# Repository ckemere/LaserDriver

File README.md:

# Glance out

The output side of **Glance**: stimulation HATs for the Raspberry Pi, their power boards, the MCU firmware and the Pi
software and OS images.  A Pi 4 with one of these HATs delivers timed optogenetic laser pulses or isolated
constant-current electrical stimulation, triggered from the Pi, a BNC input or the network, with an OLED and joystick
for use at the rig.

| | |
|---|---|
|  |  |
| **StimHAT** — isolated constant-current stimulator | **LaserDriverHAT** — laser-diode driver |
|  |  |
| **DCDCPod** — isolated ±15 V supply pod for the StimHAT | **SimpleBatteryPack** — battery ±V supply for the StimHAT |

## The boards

**StimHAT** (`hardware/StimHAT/`).  A 65 × 57 mm four-layer HAT.  The west half is the shared core: an MSPM0G1507
microcontroller on the Pi's UART with its own USB-C port and CH340N for stand-alone use, the HAT ID EEPROM, BNC
trigger in and sync out, a five-way joystick and a FIRE button, and either the Adafruit OLED bonnet stacked above or a
0.91" OLED module on the board.  The east half, behind a 2.5 mm isolation barrier crossed only by two digital
isolators, is a cathodic-first biphasic constant-current stimulator: a DAC60501 set-point, an OPA2192 current source
with a 2.49 kΩ sense resistor (502 µA full scale, 0.12 µA per code), a DG418 shorting switch between pulses and a
window comparator that latches a fault when the electrode voltage leaves ±12.35 V.  The isolated side takes its ±V
from the DCDCPod or the SimpleBatteryPack.

**LaserDriverHAT** (`hardware/LaserDriverHAT/`).  The same core with the laser-diode driver in place of the
stimulator: an MT3608 boost to 12 V, a TLV2371 current servo on a 2 Ω shunt set by the MCU's DAC (about 100 mA per
volt), a dual-FET switch pair for pulse and dummy load driven by a hardware timer, and a photodiode monitor.  The
driver block is the hand-made layout of the earlier plug-in laser module, carried over intact.

**DCDCPod** (`hardware/DCDCPod/`).  A 31 × 22.5 mm board that stands on the StimHAT between the OLED bonnet and the
BNCs: a RECOM RB-0515D/HP 5 V → ±15 V converter, an LC filter and a capacitance multiplier per rail, giving quiet
±13.5 V for the stimulator from the Pi's 5 V.

**SimpleBatteryPack** (`hardware/SimpleBatteryPack/`).  Two 4S packs in series with a centre tap, an ON/OFF switch and
a gauge, for a fully battery-powered stimulator when even the pod's residual ripple matters.

## Software

- **Firmware** (`firmware/`): one source tree builds the three MCU images (`BOARD=stim|laser|rev2`).  The MCU keeps
  the pulse timing, state machine and safety interlocks; the Pi only configures and triggers.  The binary protocol in
  `firmware/protocol.h` is mirrored by `pi/protocol.py` and cross-checked in CI.
- **Pi** (`pi/`): the `laserhat` Debian package — a C broker that owns the UART and the trigger GPIOs and accepts
  low-latency UDP triggers, an OLED daemon, a web GUI, `laserhat-flash` (programs the MCU over SWD from the Pi's
  GPIOs) and `laserhat-eeprom` (programs the HAT ID EEPROM).  The board type comes from the EEPROM; the firmware
  reports its own and the two are cross-checked.
- **Releases**: a `v*` tag makes CI build the debs and golden Raspberry Pi OS images (`laserhat-raspios-lite-*.img.xz`)
  with everything installed.  Flash an image, boot, program the EEPROM once, run `sudo laserhat-flash`.

## Getting started

1. Flash the latest release image to a card and boot the Pi with the HAT fitted.
2. Program the HAT's identity once: `sudo laserhat-eeprom write stim --yes` (or `laser`) with JP1 open, close JP1,
   reboot.  `laserhat-eeprom read` shows what the Pi sees.
3. `sudo laserhat-flash` programs the matching firmware and reports the MCU's version and board.
4. Open the web GUI (port 80 on the Pi) or use the joystick and OLED; triggers come from the FIRE button, the TRIG IN
   BNC, Pi GPIO 18, or UDP on the wired port.

`pi/PROVISIONING.md` has the details (services, network, displays, EEPROM buses), `hardware/<board>/README.md` the
design notes, pin maps and audit records of each board, `docs/REPO_MAP.md` the directory index, and `CLAUDE.md` the
working guide for agents.

## History

The first generations — a HAT with plug-in laser and e-stim modules and a relay-switched battery pack — are archived at
tag `archive/pre-glance-cleanup`, with their design history in `docs/history/REV2_NOTES.md`.  Software identifiers
(`laserhat` package, commands, services and variables) keep those names for now.

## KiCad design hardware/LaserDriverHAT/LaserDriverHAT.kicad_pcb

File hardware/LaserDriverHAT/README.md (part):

# LaserDriverHAT — the LaserHAT Rev 2 core and the LaserDaughter laser-diode driver on one Raspberry Pi HAT (rev A, 2026-10-30)

One 65 × 57 mm, 4-layer HAT derived from the StimHAT (`../StimHAT/`): the StimHAT's HAT core — MSPM0G1507, CH340N
USB-UART, USB-C power path, HAT ID EEPROM, joystick / FIRE / BSL buttons, LEDs, BNC trigger in and sync out, OLED socket,
owl — kept footprint for footprint and track for track, the isolated e-stim stimulator removed, and the laser-diode driver
of the plug-in module `../LaserDaughter/` (archived, tag `archive/pre-glance-cleanup`; rev 2.0, ordered 2026-10-01) brought in as its hand-made layout block.  The
Adafruit 4567 OLED bonnet stacks on the Pi header as on the StimHAT.  **Status: placed, the laser block's own copper
intact; the seven connections between the block and the HAT core were hand-routed by the user.  Ordered 2026-11-01 (rev 3), verified 2026-11-11 (laser output, buttons, displays).**

## Files

Generated like the StimHAT: `sch_parts.py` (single source of truth: parts, values, footprints, LCSC codes, pin → net) +
`sch_symbols.py` + `sch_engine.py` → `gen_schematic.py` writes `LaserDriverHAT.kicad_sch` and `laserdriverhat.kicad_sym`
(deterministic UUIDs: the HAT-core symbols keep the StimHAT's UUIDs).  `tools/netcheck.py` (drawing = `sch_parts`),
`tools/pcb_sync.py --keep-tracks` (headless F8, matches by reference), `tools/fresh_uuids.py`, `tools/stamp_fields.py`,
`tools/place.py` (placement table, outline, GND plane / pours, standoff keep-outs, silk, bonnet drawing; idempotent and
in sync with the board), `tools/project_settings.py` (net classes in the `.kicad_pro`; **Power1A** = the HAT core's +5V, VBUS,
VBUS_SW, +3V3, MSPM0_3V3, +3V3_PI (as on the StimHAT), +12V, /SW, LASER_V and the drive path /LD_CATHODE, /DUMMY_TOP / _MID / _BOT,
/LaserDrive, /IDrive, sized for 1 A: 0.5 mm, vias 0.8 / 0.4; `LaserDriverHAT.kicad_dru` enforces >= 0.5 mm outer / >= 1.0 mm
inner, 0.25 mm allowed on an outer layer inside an IC's courtyard for the neck-down to fine-pitch pins - the same rules as the StimHAT), `tools/make_footprints.py`
(`laserdriverhat.pretty`: MSPM0 VQFN-32, ALPS joystick, right-angle BNC; the owl G1 is `Footprints:OwlLogo_Eyes_14mm_R` from `../tools/owl_logo.py`),
`tools/make_bom.py` → `bom_LaserDriverHAT.csv`, `tools/make_fab.py` → `../fab/LaserDriverHAT/` (gerbers zip, JLC BOM / CPL,
3D renders `LaserDriverHAT_top.png` / `_bottom.png`), `tools/drc_summary.py`, `tools/fixups.py` / `maze_nets.py` / `stitch.py`
(hand-routing helpers).  The library nickname is `laserdriverhat` (was `stimhat`).  `LaserDriverHAT.kicad_dru`: one thermal
spoke allowed on the outer pours, and on R202 (see "Checks").  The StimHAT's Freerouting tools (autoroute, fan-out,
pre-route) and `board_init.py` were not carried over: they built the e-stim side.

## What changed against the StimHAT

**Removed** (schematic, board, BOM): the whole isolated half — U101 ISO7741F, U104 TLV76050, U105 DAC60501, U106 OPA2192,
U107 CD74HC4053, U108 DG418, U109 ISO1640, U110 TLV1702, R101–R121, C101–C127, D101–D104, J101 (electrodes), J102 (battery
/ DC-DC pod), J103 (pod 5 V), TP101 / TP102; the nets of the isolated side (GND_ISO, ±V_STIM, ±5V_ISO, …) and the six
HAT-side isolator lines (EN_H, CATH_H, RELEASE_H, FAULT_H, SDA_H, SCL_H); the isolation barrier (keep-out strips,
`hat_region` / `isolated_region` rule areas, the `.kicad_dru` barrier and `tht_connectors` / `j102_one_spoke` rules), the
Isolated / IsolatedPower / Rails net classes, the ISOLATED / NYLON / J102 / J103 silk, the DC-DC pod drawing.  On the board
360 StimHAT tracks / vias went with them (every one of a vanished net, BUTTON3's old route to PA15, the +5V spur to J103,
the MSPM0_3V3 branches to R107 / R108 / C103 / C101 / U101 and two MSPM0_3V3 vias left joined on In2 only); the other 450
are untouched, and all 58 HAT-core footprints are exactly where they were.

**One GND:** In1 is a single GND plane over the whole board, F / B carry full-board GND pours (0.25 mm clearance), In2 is
the routing layer it was.  MH4 no longer needs a nylon standoff.

**Kept:** everything else of the HAT core.  J7 is now **SYNC OUT** (value "BNC SYNC OUT", silk front and back, the LED
label "SYNC"): PA17 → U8B → J7 / D9 mirrors the laser pulse envelope, exactly the firmware's STIM_OUT behaviour; the net is
still `MCU_STIM_OUT`.

**Added:** the LaserDaughter's 26 fitted / jumper parts (its header sockets J1 = HAT_J8 and J3 = HAT_J9 are not fitted: their
six lines are now nets straight to U7 and the HAT's +5V / GND).  Values, footprints and LCSC codes as on the module
(`../tools/lcsc_parts.py` LASER), hand-fitted J2 (laser-diode socket) and J205 (RED shunt header), J4 (PD_K–LASER_V
solder jumper) DNP as on the module.  Reference mapping (module → HAT; the module's refs kept where the HAT core leaves
them free, +200 where R1–R26, C1–C18, U1–U8 or J5 are taken):

| Module | HAT | Part |
|---|---|---|
| R1, R2 | **R201, R202** | 100k / 33k LASER_V → DB_ADC_B divider |
| R3, R4, C11 | **R203, R204, C211** | 39k / 10k / 10 nF DB_DAC → IREF |
| R5, R6 | **R205, R206** | 187k / 10k boost feedback |
| R11, R12 | **R211, R212** | 1k 0.1 % / 4.7k photodiode → DB_ADC_A |
| C8, C9, C12 | **C208, C209, C212** | 22 µF boost in / out, 100 nF at U203 |
| U2, U3 | **U202, U203** | MT3608 boost, TLV2371 current servo |
| J5 | **J205** | RED shunt header (shorts D2) |
| D1–D4, J2, J4, L1, Q1, Q2, Rs1, SW5 | same | DSK14 ×2, KDZVTR2.7B / 2.4B, LD socket, PD jumper, 10 µH, AO9926B, NDT3055L, 2 Ω, PCM12 |
| J1, J3 | — | HAT_J8 / HAT_J9 headers, not fitted (lines become nets) |

Net names: the module's internal nets keep their names (`/SW`, `/IREF`, `/DUMMY_TOP`, `/DUMMY_MID`, `/DUMMY_BOT`,
`/LaserDrive`, `/IDrive`, `+12V`, `LASER_V`); its auto-named nets are `/LD_CATHODE` (Net-(J2-LD_Cathode)), `/PD_ANODE`,
`/PD_CATHODE`, `/Q2_GATE` (Net-(Q2-G)) and `/BOOST_FB` (Net-(U2-FB)); the header lines keep the CLAUDE.md names
`DB_PWM_A`, `DB_PWM_B`, `DB_DAC`, `DB_ADC_A`, `DB_ADC_B`.  There is no DB_GPIO / FAULT line: the laser module never had a
fault output (its J8.3 was unconnected).  Parts: 84 symbols (incl. the owl G1), 67 machine placements, 44 JLC BOM lines.

## MCU pin map (U7 MSPM0G1507, VQFN-32 RHB)

The StimHAT's map with the east column re-used for the laser and one joystick line moved; every function checked against
the MSPM0G1507 datasheet table 6-2 (SLASEW9E).  Pi-header nets unchanged.

| Pin | Port | Net | Function |
|---|---|---|---|
| 1, 2 | PA0, PA1 | I2C_SDA, I2C_SCL | I2C0 (Pi / bonnet), fixed |
| 3 / 6 / 32 | NRST / PA2 / VCORE | NRST / ROSC / VCORE | as StimHAT |
| 7 | PA3 | — | spare |
| 8 | PA4 | PI_TRIGGER | GPIO IRQ ← Pi GPIO18 (J1.12) |
| 9 | PA5 | LED_MCU | D7 |
| **10** | **PA6** | **BUTTON1** (left / BACK) | GPIO; the buttons follow the StimHAT's map (2026-10-31), off PA15 to free DAC0 |
| 11 | PA7 | BUTTON4 (up) | GPIO |
| 12, 13 | PA8, PA9 | PI_RXD, PI_TXD | UART1 ↔ Pi |
| 14, 15 | PA10, PA11 | MCU_UART_TX / RX | UART0 ↔ CH340N (BSL) |
| 16, 17, 18 | PA12, PA13, PA14 | BUTTON6 (right), BUTTON2 (centre), BUTTON3 (down) | GPIO (the StimHAT's joystick pads, shifted one pin because PA15 is the DAC here) |
| **19** | **PA15** | **DB_DAC** | **DAC0_OUT** (the only DAC0 pin): laser current set-point, ≈ 102 mA / V |
| 20 | PA16 | BUTTON5 (FIRE) | GPIO |
| 21 | PA17 | MCU_STIM_OUT | GPIO → U8B → J7 SYNC OUT |
| 22 / 23 / 24 | PA18 / PA19 / PA20 | BSL_INVOKE / SWDIO / SWCLK | fixed |
| 25 | PA21 | MCU_STIM_IN | TIMG8_C0 capture ← U8A ← J6 TRIG IN |
| 26, 27 | PA22, PA23 | — | spare (PA22 = TIMA0_C1 / ADC0 ch 7, PA23 = TIMA0_C3) |
| **28** | **PA24** | **DB_ADC_B** | **ADC0 ch 3** (A0_3): LASER_V × 33k / 133k (12 V → 2.98 V) |
| **29** | **PA25** | **DB_ADC_A** | **ADC0 ch 2** (A0_2): photodiode |
| **30** | **PA26** | **DB_PWM_A** | **TIMG7_C0** (PF 7) — laser switch (Q1 G2) |
| **31** | **PA27** | **DB_PWM_B** | **TIMG7_C1** (PF 7) — dummy switch (Q1 G1) |

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
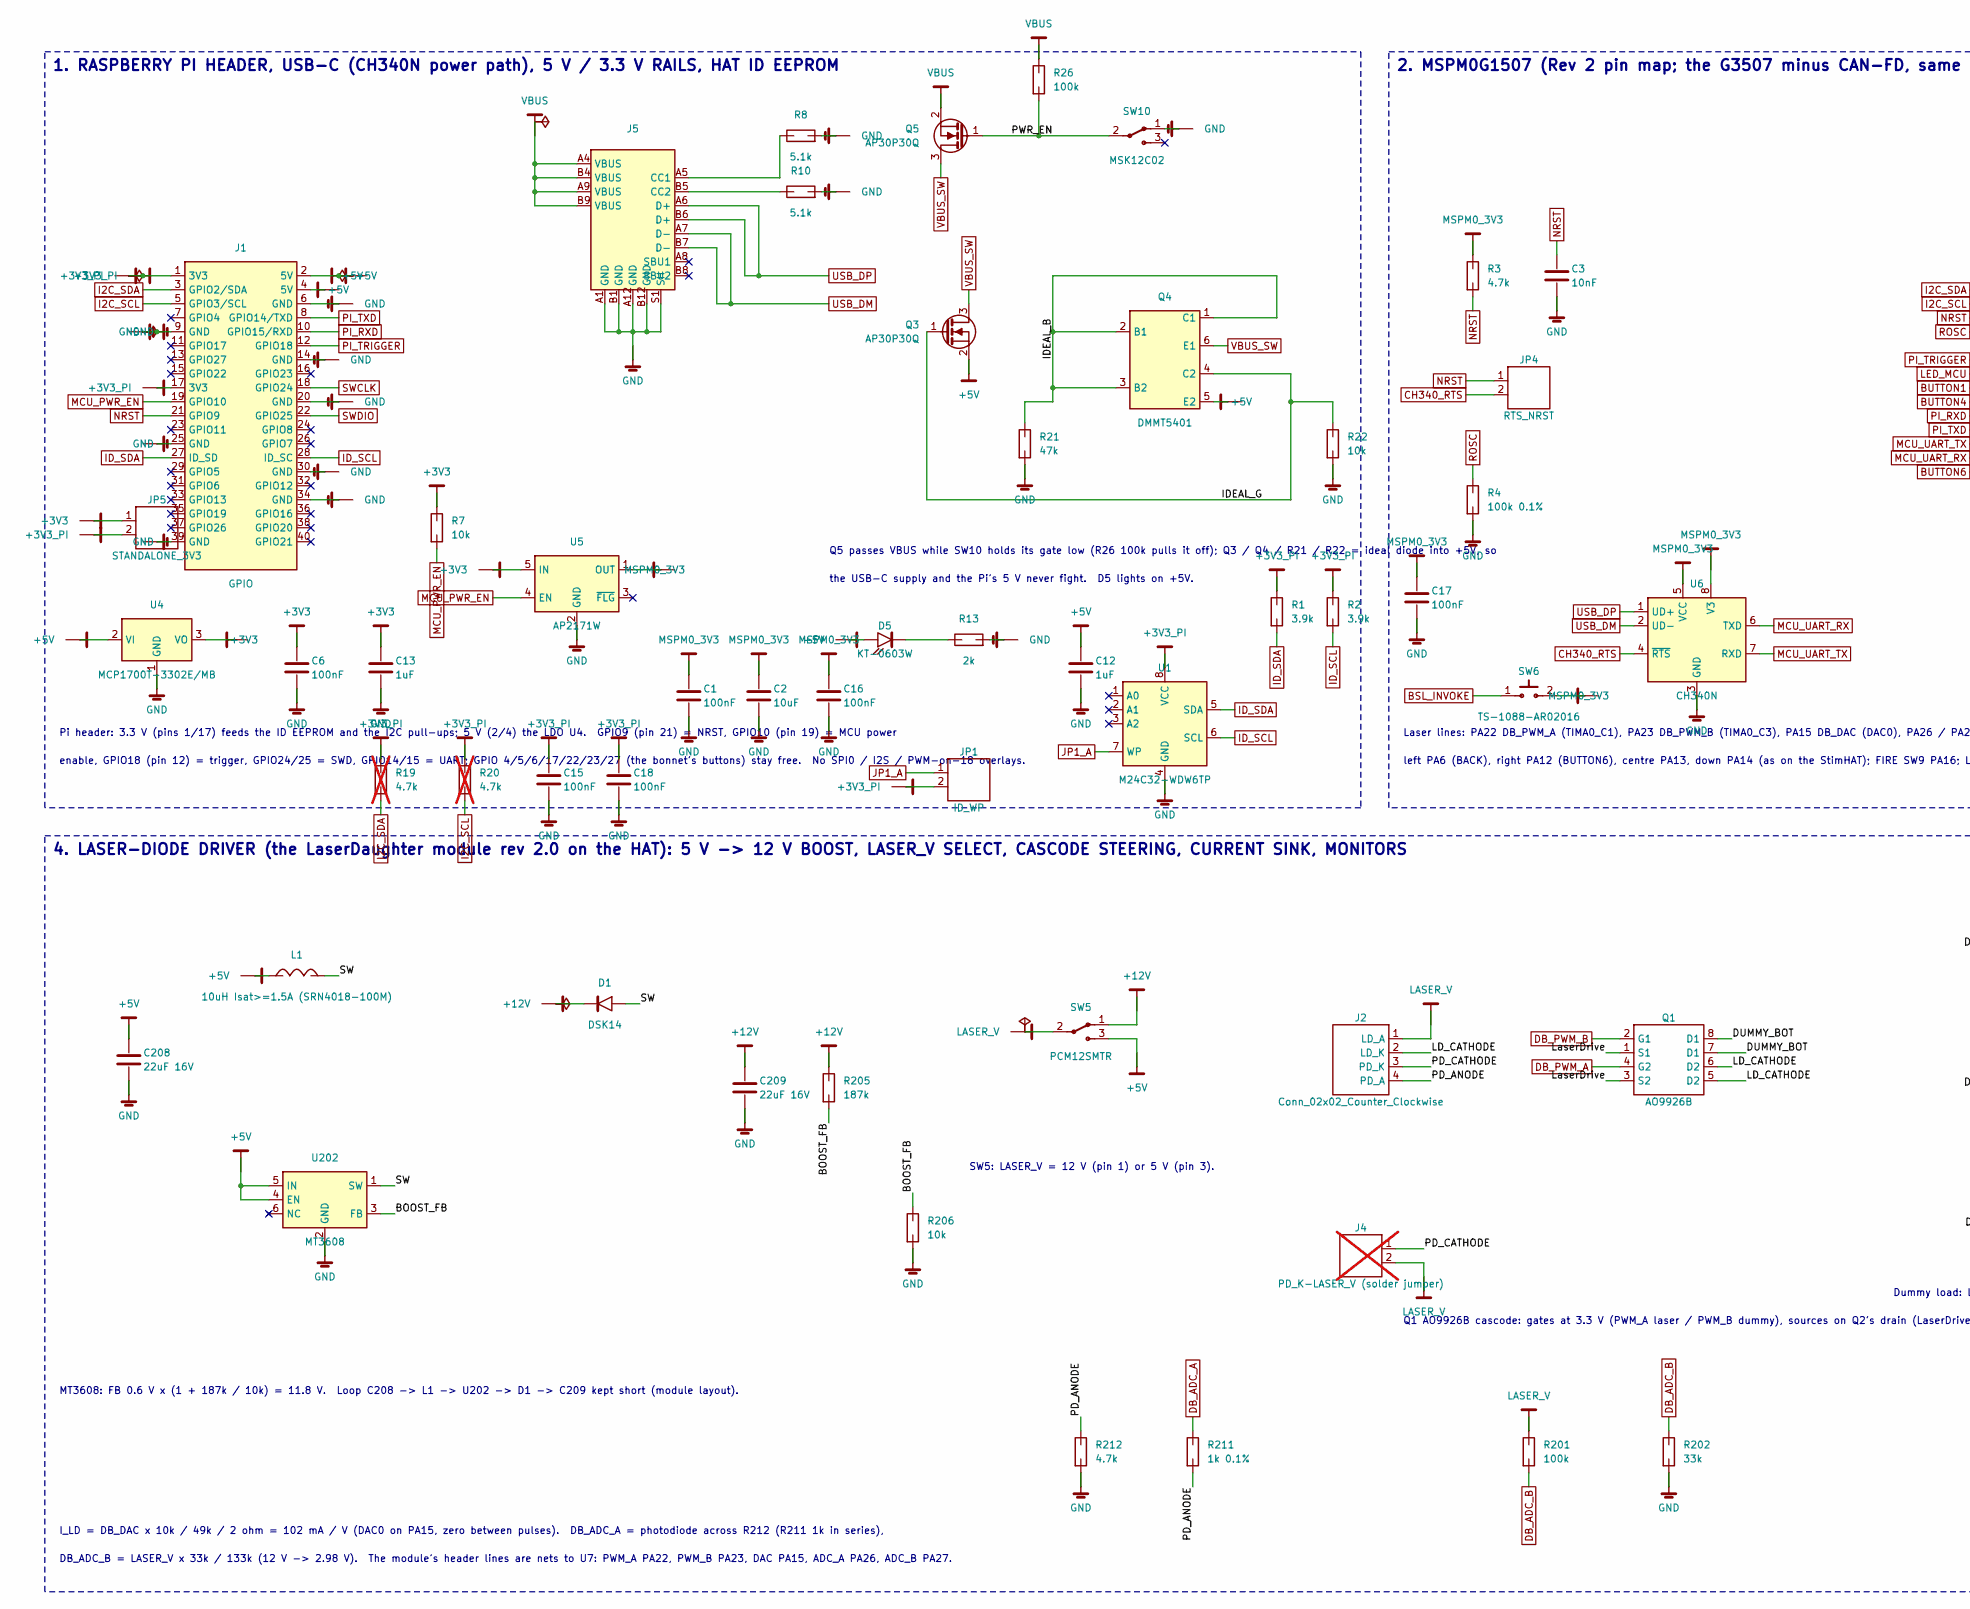
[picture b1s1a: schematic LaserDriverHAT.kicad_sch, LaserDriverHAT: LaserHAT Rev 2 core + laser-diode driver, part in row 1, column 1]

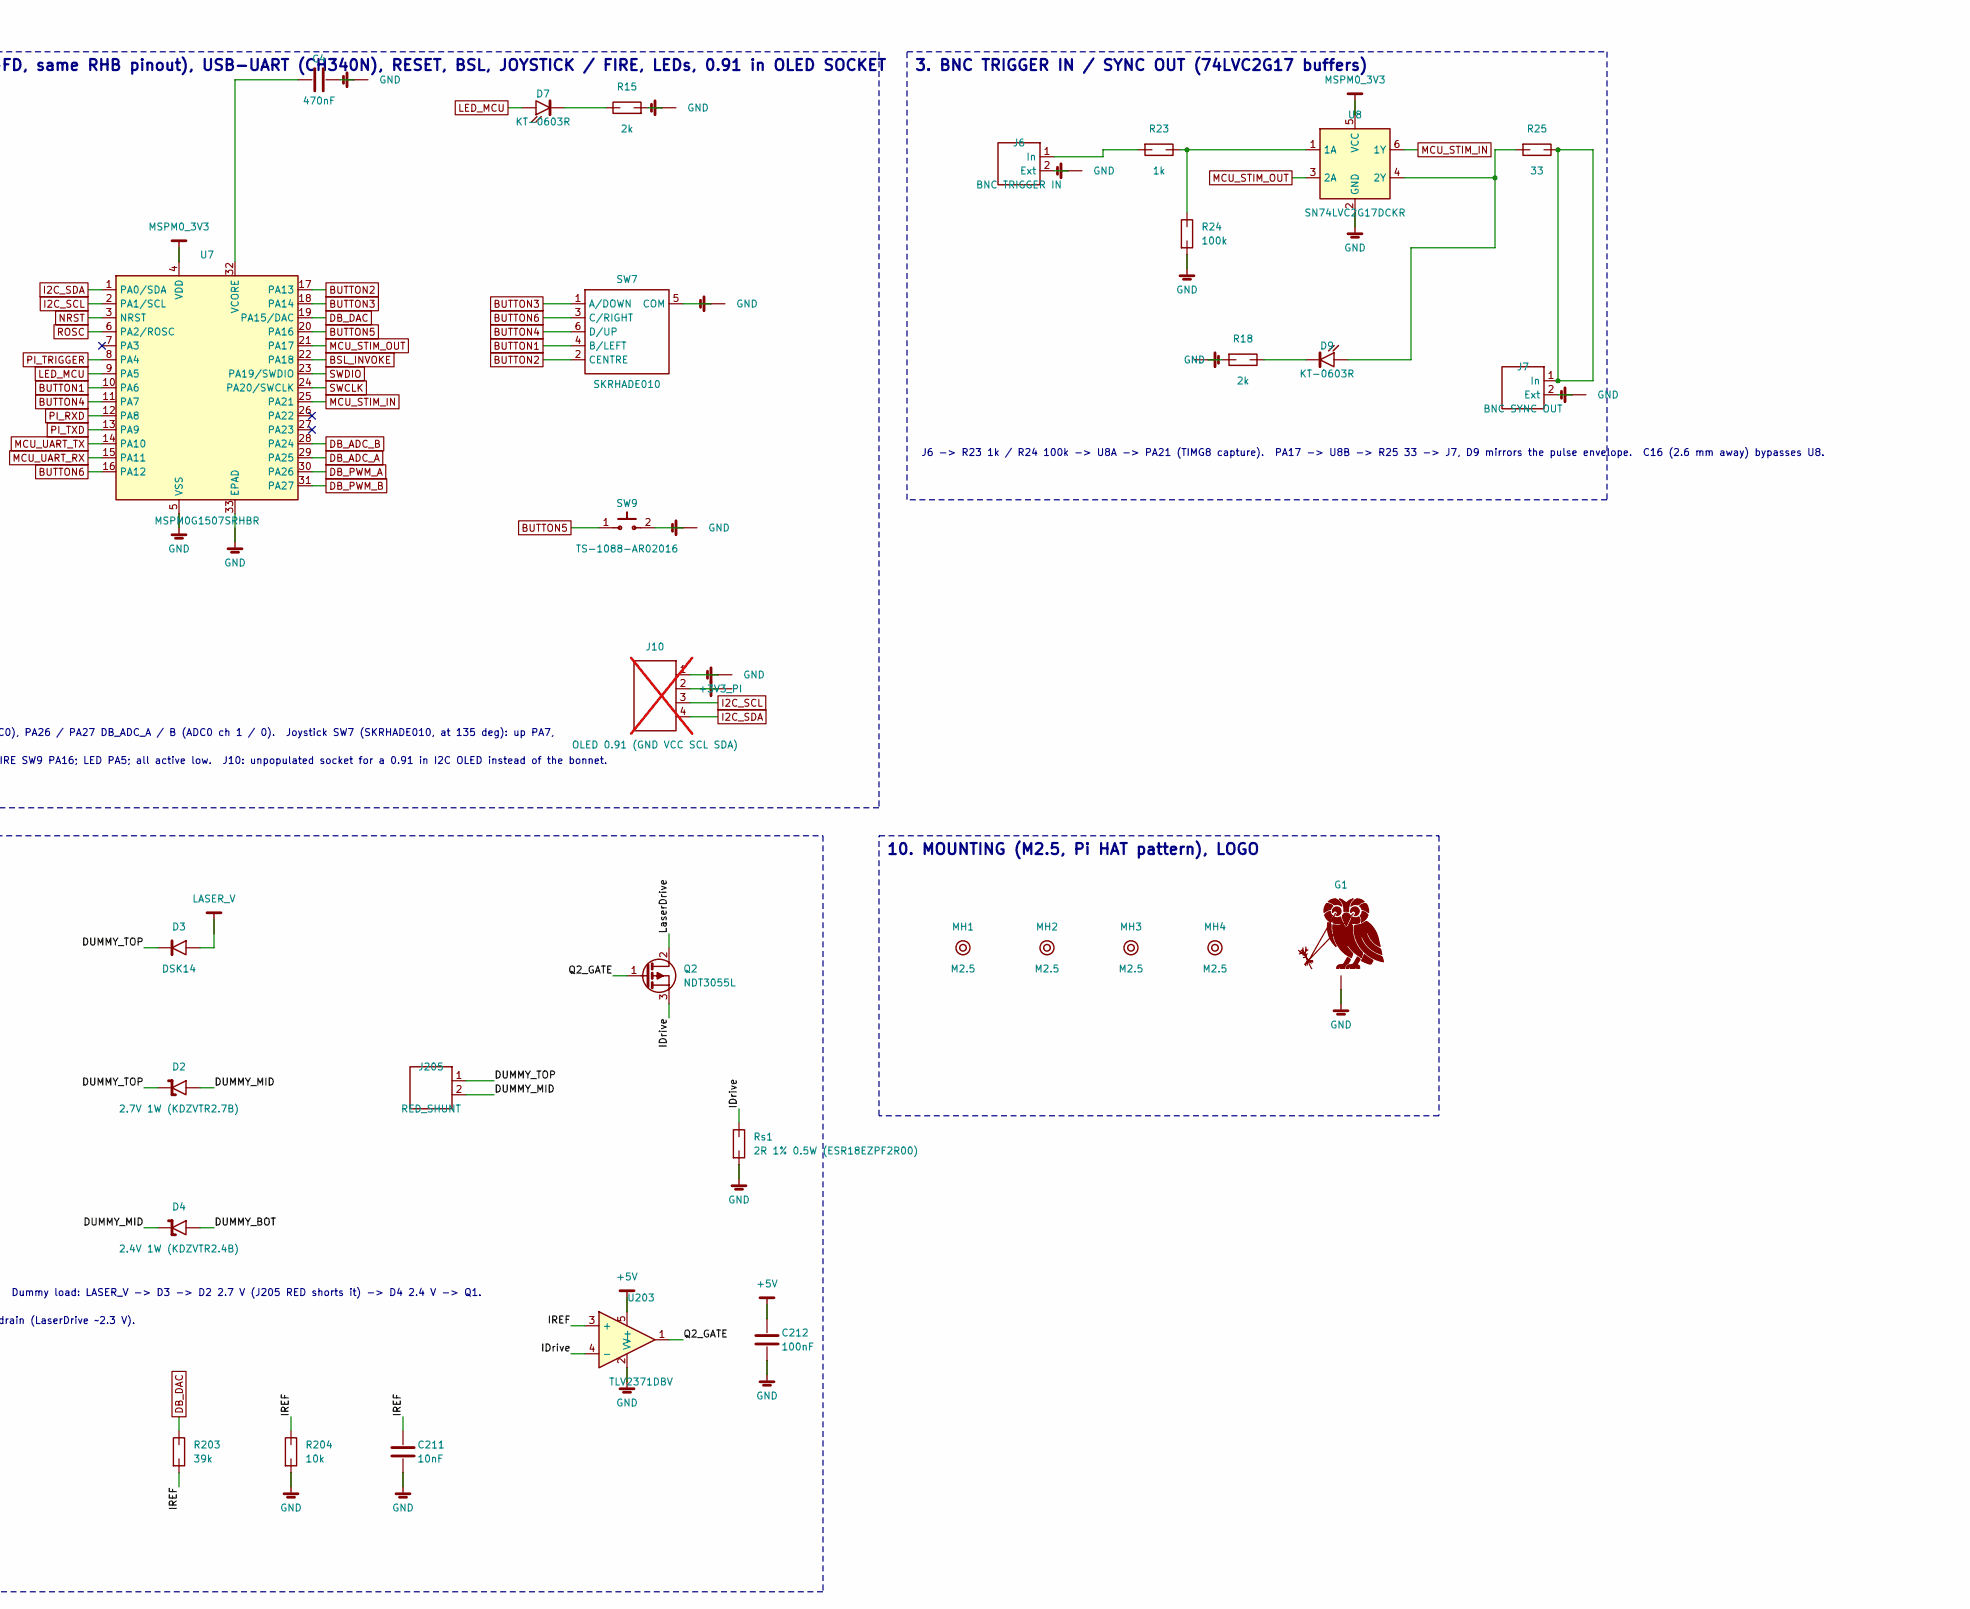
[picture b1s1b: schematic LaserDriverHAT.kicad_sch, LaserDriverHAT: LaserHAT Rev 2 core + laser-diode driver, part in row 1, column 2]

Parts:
C1, C6, C15, C16, C17, C18, C212: 100nF; C_0402_1005Metric; LCSC Part # C307331
C2: 10uF; C_0805_2012Metric; LCSC Part # C15850
C3, C211: 10nF; C_0402_1005Metric; LCSC Part # C15195
C4: 470nF; C_0402_1005Metric; LCSC Part # C47339
C12, C13: 1uF; C_0402_1005Metric; LCSC Part # C52923
C208, C209: 22uF 16V; C_1206_3216Metric; LCSC Part # C12891
D1, D3: DSK14; D_SOD-123F; LCSC Part # C37049
D2: 2.7V 1W (KDZVTR2.7B); D_SOD-123F; LCSC Part # C209583
D4: 2.4V 1W (KDZVTR2.4B); D_SOD-123F; LCSC Part # C209582
D5: KT-0603W; D_0603_1608Metric; LCSC Part # C2290
D7, D9: KT-0603R; D_0603_1608Metric; LCSC Part # C2286
G1: OwlLogo; OwlLogo_Eyes_14mm_R
J1: GPIO; Samtec_HLE-120-02-xxx-DV-BE-LC_2x20_P2.54mm_Horizontal
J2: Conn_02x02_Counter_Clockwise; PinHeader_2x02_P2.54mm_Vertical
J4: PD_K-LASER_V (solder jumper); SolderJumper-2_P1.3mm_Open_RoundedPad1.0x1.5mm; not fitted
J5: GT-USB-7010ASV; USB_C_Receptacle_G-Switch_GT-USB-7010ASV; LCSC Part # C2988369
J6: BNC TRIGGER IN; BNC_Amphenol_031-5540_RA
J7: BNC SYNC OUT; BNC_Amphenol_031-5540_RA
J10: OLED 0.91 (GND VCC SCL SDA); PinSocket_1x04_P2.54mm_Vertical; not fitted
J205: RED_SHUNT; PinHeader_1x02_P2.00mm_Vertical
JP1: ID_WP; SolderJumper-2_P1.3mm_Open_RoundedPad1.0x1.5mm
JP4: RTS_NRST; SolderJumper-2_P1.3mm_Open_TrianglePad1.0x1.5mm
JP5: STANDALONE_3V3; SolderJumper-2_P1.3mm_Open_RoundedPad1.0x1.5mm
L1: 10uH Isat>=1.5A (SRN4018-100M); L_Bourns-SRN4018; LCSC Part # C503307
MH1, MH2, MH3, MH4: M2.5; MountingHole_2.7mm_M2.5
Q1: AO9926B; SOIC-8_3.9x4.9mm_P1.27mm; LCSC Part # C428343
Q2: NDT3055L; SOT-223-3_TabPin2; LCSC Part # C274612
Q3, Q5: AP30P30Q; PDFN3333-8_PMOS_GSD; LCSC Part # C471913
Q4: DMMT5401; SOT-23-6; LCSC Part # C154733
R1, R2: 3.9k; R_0402_1005Metric; LCSC Part # C51721
R3, R212: 4.7k; R_0402_1005Metric; LCSC Part # C25900
R4: 100k 0.1%; R_0402_1005Metric; LCSC Part # C852472
R7, R22, R204, R206: 10k; R_0402_1005Metric; LCSC Part # C25744
R8, R10: 5.1k; R_0402_1005Metric; LCSC Part # C25905
R13, R15, R18: 2k; R_0402_1005Metric; LCSC Part # C4109
R19, R20: 4.7k; R_0402_1005Metric; LCSC Part # C25900; not fitted
R21: 47k; R_0402_1005Metric; LCSC Part # C25792
R23: 1k; R_0402_1005Metric; LCSC Part # C11702
R24, R26, R201: 100k; R_0402_1005Metric; LCSC Part # C25741
R25: 33; R_0402_1005Metric; LCSC Part # C25105
R202: 33k; R_0402_1005Metric; LCSC Part # C25779
R203: 39k; R_0402_1005Metric; LCSC Part # C25783
R205: 187k; R_0402_1005Metric; LCSC Part # C25761
R211: 1k 0.1%; R_0402_1005Metric; LCSC Part # C852624
Rs1: 2R 1% 0.5W (ESR18EZPF2R00); R_1206_3216Metric; LCSC Part # C2105197
SW5: PCM12SMTR; SW_SPDT_PCM12; LCSC Part # C221841
SW6, SW9: TS-1088-AR02016; SW_SPST_TS-1088-xR020; LCSC Part # C720477
SW7: SKRHADE010; SW_ALPS_SKRHADE010; LCSC Part # C202415
SW10: MSK12C02; SW_SPDT_Shouhan_MSK12C02; LCSC Part # C431540
U1: M24C32-WDW6TP; TSSOP-8_4.4x3mm_P0.65mm; LCSC Part # C283445
U4: MCP1700T-3302E/MB; SOT-89-3; LCSC Part # C632000
U5: AP2171W; SOT-23-5; LCSC Part # C110466
U6: CH340N; JEITA_SOIC-8_3.9x4.9mm_P1.27mm; LCSC Part # C2977777
U7: MSPM0G1507SRHBR; VQFN32_RHB_TEX; LCSC Part # C22406180
U8: SN74LVC2G17DCKR; SOT-363_SC-70-6; LCSC Part # C50714
U202: MT3608; SOT-23-6; LCSC Part # C84817
U203: TLV2371DBV; SOT-23-5; LCSC Part # C55940

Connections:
+3V3: C6.1, C13.1, JP5.1 (A), R7.1, U4.3 (VO), U5.5 (IN)
+3V3_PI: C15.1, C18.1, J1.1 (3V3), J1.17 (3V3), J10.2, JP1.2 (B), JP5.2 (B), R1.1, R2.1, R19.1, R20.1, U1.8 (VCC)
+5V: C12.1, C208.1, C212.1, D5.2 (A), J1.2 (5V), J1.4 (5V), L1.1, Q3.2 (S), Q4.5 (E2), SW5.3 (B), U4.2 (VI), U202.4 (EN), U202.5 (IN), U203.5 (V+)
+12V: C209.1, D1.1 (K), R205.1, SW5.1 (A)
/BOOST_FB: R205.2, R206.1, U202.3 (FB)
/DUMMY_BOT: D4.2 (A), Q1.7 (D1), Q1.8 (D1)
/DUMMY_MID: D2.2 (A), D4.1 (K), J205.2
/DUMMY_TOP: D2.1 (K), D3.1 (K), J205.1
/IDEAL_B: Q4.1 (C1), Q4.2 (B1), Q4.3 (B2), R21.1
/IDEAL_G: Q3.1 (G), Q4.4 (C2), R22.1
/IDrive: Q2.3 (S), Rs1.1, U203.4 (-)
/IREF: C211.1, R203.2, R204.1, U203.3 (+)
/LD_CATHODE: J2.2 (LD_K), Q1.5 (D2), Q1.6 (D2)
/LaserDrive: Q1.1 (S1), Q1.3 (S2), Q2.2 (D)
/PD_ANODE: J2.4 (PD_A), R211.2, R212.1
/PD_CATHODE: J2.3 (PD_K), J4.1 (A)
/PWR_EN: Q5.1 (G), R26.2, SW10.2 (C)
/Q2_GATE: Q2.1 (G), U203.1
/SW: D1.2 (A), L1.2, U202.1 (SW)
BSL_INVOKE: SW6.1, U7.22 (PA18)
BUTTON1: SW7.4 (B/LEFT), U7.10 (PA6)
BUTTON2: SW7.2 (CENTRE), U7.17 (PA13)
BUTTON3: SW7.1 (A/DOWN), U7.18 (PA14)
BUTTON4: SW7.6 (D/UP), U7.11 (PA7)
BUTTON5: SW9.1, U7.20 (PA16)
BUTTON6: SW7.3 (C/RIGHT), U7.16 (PA12)
CH340_RTS: JP4.2 (B), U6.4 (~RTS)
DB_ADC_A: R211.1, U7.29 (PA25)
DB_ADC_B: R201.2, R202.1, U7.28 (PA24)
DB_DAC: R203.1, U7.19 (PA15/DAC)
DB_PWM_A: Q1.4 (G2), U7.30 (PA26)
DB_PWM_B: Q1.2 (G1), U7.31 (PA27)
GND: C1.2, C2.2, C3.2, C4.2, C6.2, C12.2, C13.2, C15.2, C16.2, C17.2, C18.2, C208.2, C209.2, C211.2, C212.2, G1.1 (GND), J1.6 (GND), J1.9 (GND), J1.14 (GND), J1.20 (GND), J1.25 (GND), J1.30 (GND), J1.34 (GND), J1.39 (GND), J5.A1 (GND), J5.A12 (GND), J5.B1 (GND), J5.B12 (GND), J5.S1 (SH), J6.2 (Ext), J7.2 (Ext), J10.1, R4.2, R8.2, R10.2, R13.2, R15.2, R18.2, R21.2, R22.2, R24.2, R202.2, R204.2, R206.2, R212.2, Rs1.2, SW7.5 (COM), SW9.2, SW10.1 (A), U1.4 (GND), U4.1 (GND), U5.2 (GND), U6.3 (GND), U7.5 (VSS), U7.33 (EPAD), U8.2 (GND), U202.2 (GND), U203.2 (V-)
I2C_SCL: J1.5 (GPIO3/SCL), J10.3, R20.2, U7.2 (PA1/SCL)
I2C_SDA: J1.3 (GPIO2/SDA), J10.4, R19.2, U7.1 (PA0/SDA)
ID_SCL: J1.28 (ID_SC), R2.2, U1.6 (SCL)
ID_SDA: J1.27 (ID_SD), R1.2, U1.5 (SDA)
JP1_A: JP1.1 (A), U1.7 (WP)
LASER_V: D3.2 (A), J2.1 (LD_A), J4.2 (B), R201.1, SW5.2 (C)
LED_MCU: D7.2 (A), U7.9 (PA5)
MCU_PWR_EN: J1.19 (GPIO10), R7.2, U5.4 (EN)
MCU_STIM_IN: U7.25 (PA21), U8.6 (1Y)
MCU_STIM_OUT: U7.21 (PA17), U8.3 (2A)
MCU_UART_RX: U6.6 (TXD), U7.15 (PA11)
MCU_UART_TX: U6.7 (RXD), U7.14 (PA10)
MSPM0_3V3: C1.1, C2.1, C16.1, C17.1, R3.1, SW6.2, U5.1 (OUT), U6.5 (VCC), U6.8 (V3), U7.4 (VDD), U8.5 (VCC)
NRST: C3.1, J1.21 (GPIO9), JP4.1 (A), R3.2, U7.3 (NRST)
unnamed: D5.1 (K), R13.1
unnamed: D7.1 (K), R15.1
unnamed: D9.2 (A), R25.2, U8.4 (2Y)
unnamed: D9.1 (K), R18.1
unnamed: J5.A5 (CC1), R8.1
unnamed: J5.B5 (CC2), R10.1
unnamed: J6.1 (In), R23.2
unnamed: J7.1 (In), R25.1
unnamed: C4.1, U7.32 (VCORE)
unnamed: R23.1, R24.1, U8.1 (1A)
PI_RXD: J1.10 (GPIO15/RXD), U7.12 (PA8)
PI_TRIGGER: J1.12 (GPIO18), U7.8 (PA4)
PI_TXD: J1.8 (GPIO14/TXD), U7.13 (PA9)
ROSC: R4.1, U7.6 (PA2/ROSC)
SWCLK: J1.18 (GPIO24), U7.24 (PA20/SWCLK)
SWDIO: J1.22 (GPIO25), U7.23 (PA19/SWDIO)
USB_DM: J5.A7 (D-), J5.B7 (D-), U6.2 (UD-)
USB_DP: J5.A6 (D+), J5.B6 (D+), U6.1 (UD+)
VBUS: J5.A4 (VBUS), J5.A9 (VBUS), J5.B4 (VBUS), J5.B9 (VBUS), Q5.2 (S), R26.1
VBUS_SW: Q3.3 (D), Q4.6 (E1), Q5.3 (D)

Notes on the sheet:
Pi header: 3.3 V (pins 1/17) feeds the ID EEPROM and the I2C pull-ups; 5 V (2/4) the LDO U4. GPIO9 (pin 21) = NRST, GPIO10 (pin 19) = MCU power
SW5: LASER_V = 12 V (pin 1) or 5 V (pin 3).
3. BNC TRIGGER IN / SYNC OUT (74LVC2G17 buffers)
J6 -> R23 1k / R24 100k -> U8A -> PA21 (TIMG8 capture). PA17 -> U8B -> R25 33 -> J7, D9 mirrors the pulse envelope. C16 (2.6 mm away) bypasses U8.
Q5 passes VBUS while SW10 holds its gate low (R26 100k pulls it off); Q3 / Q4 / R21 / R22 = ideal diode into +5V, so
1. RASPBERRY PI HEADER, USB-C (CH340N power path), 5 V / 3.3 V RAILS, HAT ID EEPROM
I_LD = DB_DAC x 10k / 49k / 2 ohm = 102 mA / V (DAC0 on PA15, zero between pulses). DB_ADC_A = photodiode across R212 (R211 1k in series),
enable, GPIO18 (pin 12) = trigger, GPIO24/25 = SWD, GPIO14/15 = UART; GPIO 4/5/6/17/22/23/27 (the bonnet's buttons) stay free. No SPI0 / I2S / PWM-on-18 overlays.
Laser lines: PA22 DB_PWM_A (TIMA0_C1), PA23 DB_PWM_B (TIMA0_C3), PA15 DB_DAC (DAC0), PA26 / PA27 DB_ADC_A / B (ADC0 ch 1 / 0). Joystick SW7 (SKRHADE010, at 135 deg): up PA7,
2. MSPM0G1507 (Rev 2 pin map; the G3507 minus CAN-FD, same RHB pinout), USB-UART (CH340N), RESET, BSL, JOYSTICK / FIRE, LEDs, 0.91 in OLED SOCKET
10. MOUNTING (M2.5, Pi HAT pattern), LOGO
Dummy load: LASER_V -> D3 -> D2 2.7 V (J205 RED shorts it) -> D4 2.4 V -> Q1.
DB_ADC_B = LASER_V x 33k / 133k (12 V -> 2.98 V). The module's header lines are nets to U7: PWM_A PA22, PWM_B PA23, DAC PA15, ADC_A PA26, ADC_B PA27.
4. LASER-DIODE DRIVER (the LaserDaughter module rev 2.0 on the HAT): 5 V -> 12 V BOOST, LASER_V SELECT, CASCODE STEERING, CURRENT SINK, MONITORS
left PA6 (BACK), right PA12 (BUTTON6), centre PA13, down PA14 (as on the StimHAT); FIRE SW9 PA16; LED PA5; all active low. J10: unpopulated socket for a 0.91 in I2C OLED instead of the bonnet.
the USB-C supply and the Pi's 5 V never fight. D5 lights on +5V.
Q1 AO9926B cascode: gates at 3.3 V (PWM_A laser / PWM_B dummy), sources on Q2's drain (LaserDrive ~2.3 V).
MT3608: FB 0.6 V x (1 + 187k / 10k) = 11.8 V. Loop C208 -> L1 -> U202 -> D1 -> C209 kept short (module layout).

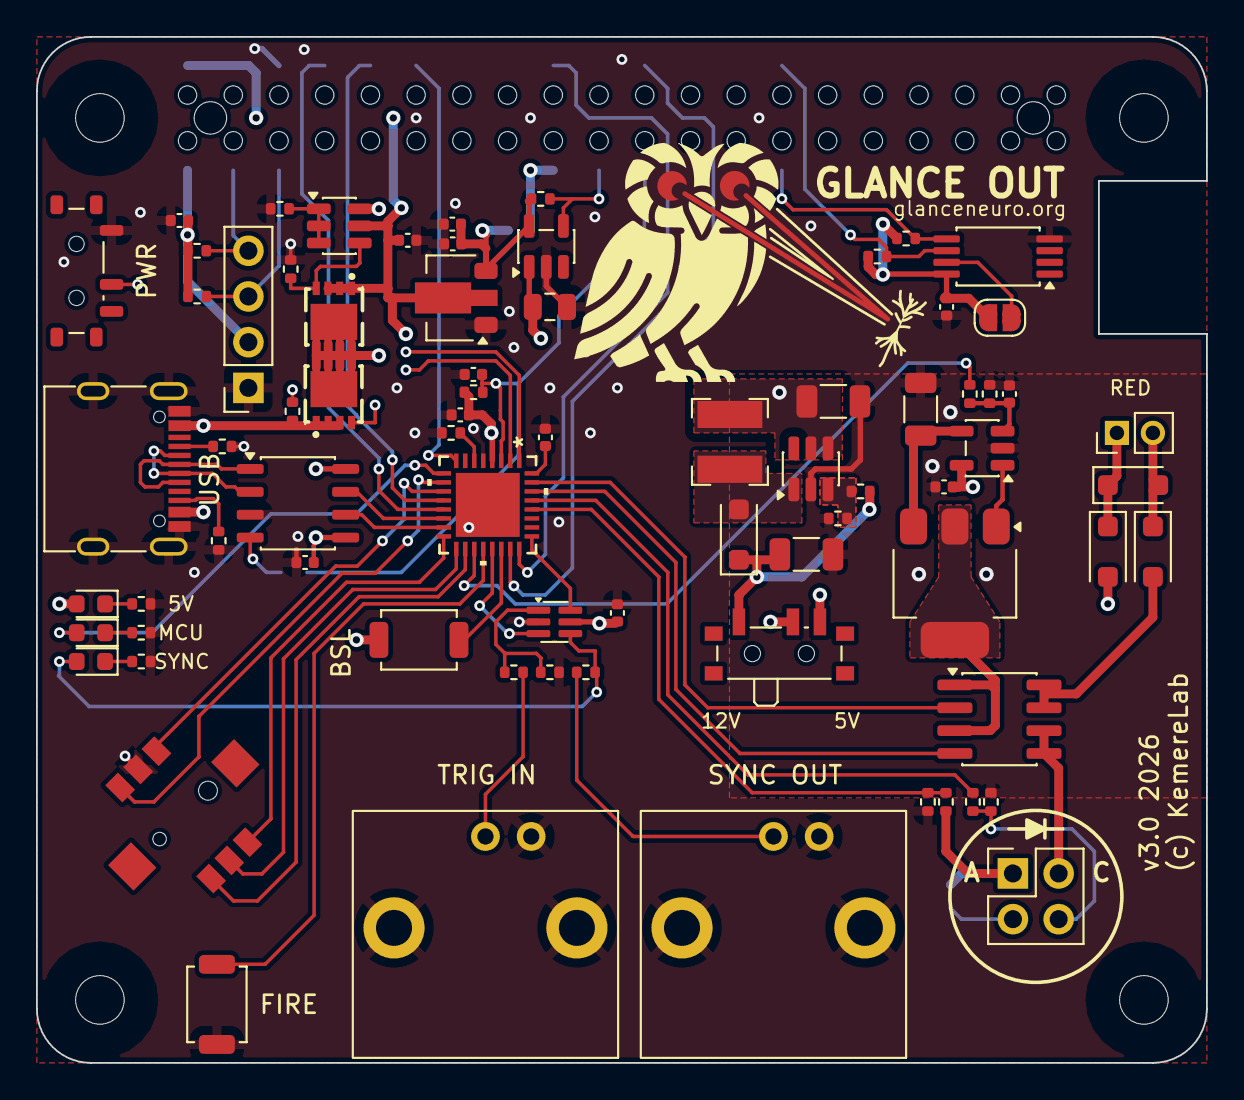
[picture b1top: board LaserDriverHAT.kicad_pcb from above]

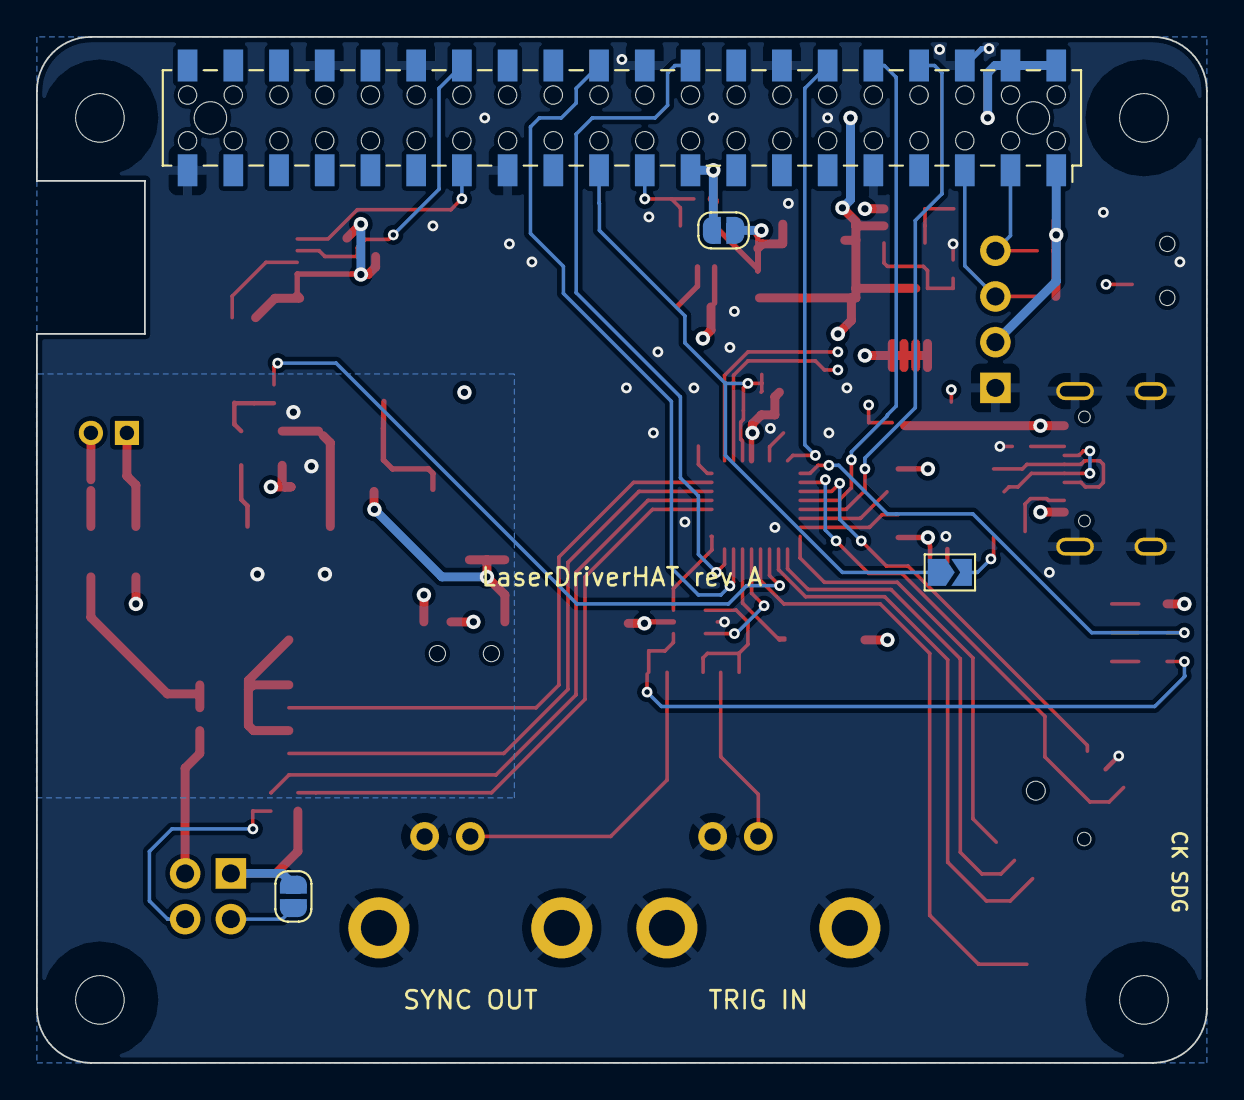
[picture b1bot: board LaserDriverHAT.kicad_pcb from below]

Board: 4 copper layers, 65.0 x 57.0 mm, 84 parts (4 on the bottom side), 67 nets.

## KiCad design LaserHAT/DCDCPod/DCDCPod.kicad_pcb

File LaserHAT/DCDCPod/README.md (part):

# DCDCPod — isolated ±15 V supply pod for the StimHAT (rev A, 2026-10-29; turned around 2026-10-30)

The isolated supply that left the StimHAT on 2026-10-29 (StimHAT/README.md, "The DC-DC pod"): a Mornsun A0515S-1WR3
(5 V → ±15 V, 1 W), its 4.7 µF input capacitor, a 10 µH / 10 µF LC filter per rail and an NPN / PNP capacitance
multiplier per rail (≈ 0.6 V drop, ≈ 60 dB ripple rejection above 100 Hz), on a 31 × 22.5 mm two-layer 1.6 mm
board that **stands vertically on the StimHAT's top side** in the band north of the BNC bodies, parts face south, PS1
along its top edge hanging over the BNC bodies, and plugs into the HAT with two right-angle pin headers on its bottom
edge: J1 (1 × 2, 2.54 mm) into J103 (5 V / GND) and J2 (1 × 4, 2.0 mm) into the
holes of J102 (+V / 0V / −V / CAB; the JST socket is not fitted when the pod is used).  No output capacitors: the HAT
keeps C109 / C110 and the 20 V clamps.  Generated like the battery pack and the StimHAT; not ordered.

Files: `gen_schematic.py` + `sch_parts.py` + `sch_symbols.py` + `sch_engine.py` → `DCDCPod.kicad_sch` (deterministic
UUIDs, ERC 0 / 0) and `dcdcpod.kicad_sym`; `tools/netcheck.py` proves the drawing equals `sch_parts.PARTS`;
`tools/ref/DCDCPod.net` is the exported netlist; `tools/make_footprints.py` → `dcdcpod.pretty` (the StimHAT's
`DCDC_SIP6_A0515S_BodyN` with its VRML model in `dcdcpod.3dshapes`, and copies of KiCad's two horizontal pin headers
without the pin drawing beyond the body and without the silk pin-1 mark, mirrored along the pin row so that pad 1 is
at the far end of the row — see Mechanical); `fp-lib-table` points only at `dcdcpod.pretty`
(everything else is KiCad's standard library).  Board: `tools/board_init.py` (once: rules, net classes, footprints from the
netlist via `tools/pcb_sync.py`; `--reload J1 J2` re-loads footprints that `make_footprints.py` changed),
`tools/place.py` (placement, outline, barrier rule areas, silk; idempotent),
`tools/route.py` (scripted tracks, 0.3 mm, no vias; idempotent), `tools/project_settings.py` (classes / constraints into
the `.kicad_pro`), `tools/fresh_uuids.py`, `tools/stamp_fields.py` (LCSC field onto the footprints),
`tools/drc_summary.py`, `tools/check_isolation.py` (see Checks), `tools/make_fab.py` → `../fab/DCDCPod/` (gerbers, JLC BOM + CPL,
top / bottom / perspective renders, README).  `DCDCPod_schematic.pdf` is the drawing.  Python: `~/.venvs/kicad/bin/python` for the pcbnew scripts.

## Circuit

| Block | Parts | Nets |
|---|---|---|
| 5 V in | J1 pin 1 = 5 V, pin 2 = GND (into HAT J103); C104 4.7 µF 0603 (C69335) | +5V, GND |
| Converter | PS1 A0515S-1WR3, SIP, pins 1 +Vin, 2 −Vin, 4 −Vo, 5 0V, 6 +Vo; hand-fitted, no LCSC code (RECOM RB-0515D/HP is pin-compatible) | +V_RAW, 0V, −V_RAW |
| Filter | L101 / L102 10 µH 0805 (C139245) in series with +Vo / −Vo, C105 / C106 10 µF 25 V 0805 (C15850) after them to 0V | +V_F, −V_F |
| Multipliers | Q101 MMBT3904 (C20526): C = +V_F, B from +V_F through R111 4.7 k (C25900) with C107 10 µF to 0V, E = +V_OUT; Q102 MMBT3906 (C53444) mirror image on −V_F with R112 / C108, E = −V_OUT | QB_P, QB_N, +V_OUT, −V_OUT |
| Out | J2 (into HAT J102's holes): **pin 1 = CAB (= 0V), 2 = −V_OUT, 3 = 0V, 4 = +V_OUT** — the mirror of the HAT's J102 numbering (1 = +V … 4 = CAB); pin 1 (square pad) is the west-most pin, on HAT x 38 (unchanged since rev A was drawn facing north: the mirrored header footprint keeps the pin → net table) | |
| Test points | TP1 +V_OUT, TP2 0V, TP3 −V_OUT: 1.0 mm pads **on the back** over J2 (the back faces the bonnet, 5 mm away; reachable with the pod unplugged) | |

Load: the stimulator draws ≈ 10 mA per rail, well above the A0515S's 10 % minimum (3.3 mA at 1 W); the multipliers
drop ≈ 0.6 V, so expect ≈ ±14 V at the HAT's J102.  All three codes not already in `../tools/lcsc_catalog.json` were
looked up at JLC on 2026-10-29: C20526 = MMBT3904 (basic), C53444 = onsemi MMBT3906LT1G (extended), C139245 = Fenghua
CMP201209XD100MT 10 µH 0805 (extended).

## Mechanical: how the pod sits on the HAT (since 2026-10-30)

Pod coordinates: x 0–31 runs along the HAT's band, y 0–22.5 runs down the pod (y 22.5 = bottom edge, 0.5 mm above
the HAT's surface; height above the HAT **z = 23.0 − pod y**).  The front (F.Cu, every part) faces **south**, toward
the BNC bodies, and is seen from the south, so HAT east is on the right: **HAT x = pod x + 15** (the pod still covers
HAT x 15–46).  The HAT's free band is x 15–46, y 36.5–43.1 (parts ≤ 1 mm) with the J102 / J103 rows at **y 39.0**, the
BNC bodies (15.6 mm tall) from y 43.1 and the OLED bonnet (PCB at z 9–10.6) over y < 31.0.

| | pod (x, y) | net | HAT x | HAT hole |
|---|---|---|---|---|
| J1.1 | (4.00, 18.10) | +5V | 19.00 | J103.1 5 V |
| J1.2 | (6.54, 18.10) | GND | 21.54 | J103.2 GND |
| J2.1 | (23.00, 18.90) | 0V (CAB) | 38.00 | J102.4 CAB |
| J2.2 | (25.00, 18.90) | −V_OUT | 40.00 | J102.3 −V |
| J2.3 | (27.00, 18.90) | 0V | 42.00 | J102.2 0V |
| J2.4 | (29.00, 18.90) | +V_OUT | 44.00 | J102.1 +V |

Same nets on the same HAT holes as rev A facing north; J1.1 → J2.1 = 19.00 mm, J1.1 → J2.4 = 25.00 mm (checked by
`tools/check_isolation.py`, pin by pin with its net).  Both headers are rotated 270° (pins toward the bottom edge).  A
right-angle header on the front with its pins pointing down numbers its pins westward, which would have reversed both
headers on the HAT; `tools/make_footprints.py` therefore mirrors the two header footprints along their row (pad 1 at
the far end, pad N at the origin; the header is symmetric, so pads, body and 3D model land in the same places) and the
schematic keeps its pin → net table.  J2's pads are 3.6 mm above the edge (its 2.0 mm header has 4.2 mm tails: 3.6 mm
reach below the edge → ≈ 3 mm into the HAT, 1.5 mm out of its underside), J1's 4.4 mm (6 mm tails → ≈ 5 mm into the
HAT: trim after soldering) — as in rev A.

**Depth (HAT y).**  KiCad's models of the two headers put the horizontal pin 1.27 mm (2.54 mm header) and 1.00 mm (2.0 mm
header) in front of the board, so with both pin rows in the HAT's holes at y 39.0 the pod's front face is at HAT y
37.73 (J1) – 38.00 (J2), nominally 37.87 with each pin 0.13 mm off its hole centre (taken up by the hole slack / pin
flex; J102's holes are 0.75–0.8 mm for 0.5 mm square pins, so fit J2 first).  The board sits **north** of its pins.

| | value |
|---|---|
| pod height | 22.5 mm (bottom edge z 0.5, top edge z 23.0) |
| board | 1.6 mm; back face at HAT y 36.13–36.40 (nominal 36.27) |
| back → bonnet PCB edge (y 31.0) | **5.1–5.4 mm** (and the bonnet is at z 9–10.6) |
| front → BNC bodies (y 43.1) | 5.1–5.4 mm; below PS1 nothing stands more than 2.54 mm out of the face (J1's body; J2's 2.0, 0805s ≈ 1.3) |
| PS1 pin row | pod y 1.3, z 21.7 |
| PS1 body (6.00 mm along the pod: 0.9 mm above / 5.1 mm below the pin row) | pod y 0.4–6.4, **z 16.6–22.6** (0.4 mm inside the top edge) |
| PS1 body → BNC body tops (15.6 mm) | **1.0 mm** |
| PS1 body depth (10.16 mm out of the face) | HAT y ≈ 37.9 → 48.0, i.e. ≈ 4.9 mm over the BNC bodies (J6 and the west end of J7; PS1 covers HAT x 16.4–36.0) |

PS1's body is the only thing south of y 40.3 and it is 1.0 mm above the BNC bodies; nothing on the pod reaches north of
its back except the header tails and solder (≈ 3 mm, at z 4–5, under the bonnet's height).  The 1.6 mm board needs no
clipped tails and no low fillets any more (rev A's 1.2 mm board and those rules existed only for its 0.66 mm back
clearance to the BNC bodies); the 2.0 mm header's 1.5 mm protrusion under the HAT is unchanged.

**Layout.**  PS1 at (3.6, 1.3) rot 0 along the top edge: pins 1 / 2 (+Vin, GND) at x 3.6 / 6.14 on the 5 V side, pins
4 / 5 / 6 (−Vo, 0V, +Vo) at x 11.22 / 13.76 / 16.3 on the isolated side, body below the pin row (pod y 0.4–6.4, marked
face down toward the HAT).  5 V side (x < 7.43): +5V and GND straight down x 3.6 / 6.14 to J1, C104 (0603) across them
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
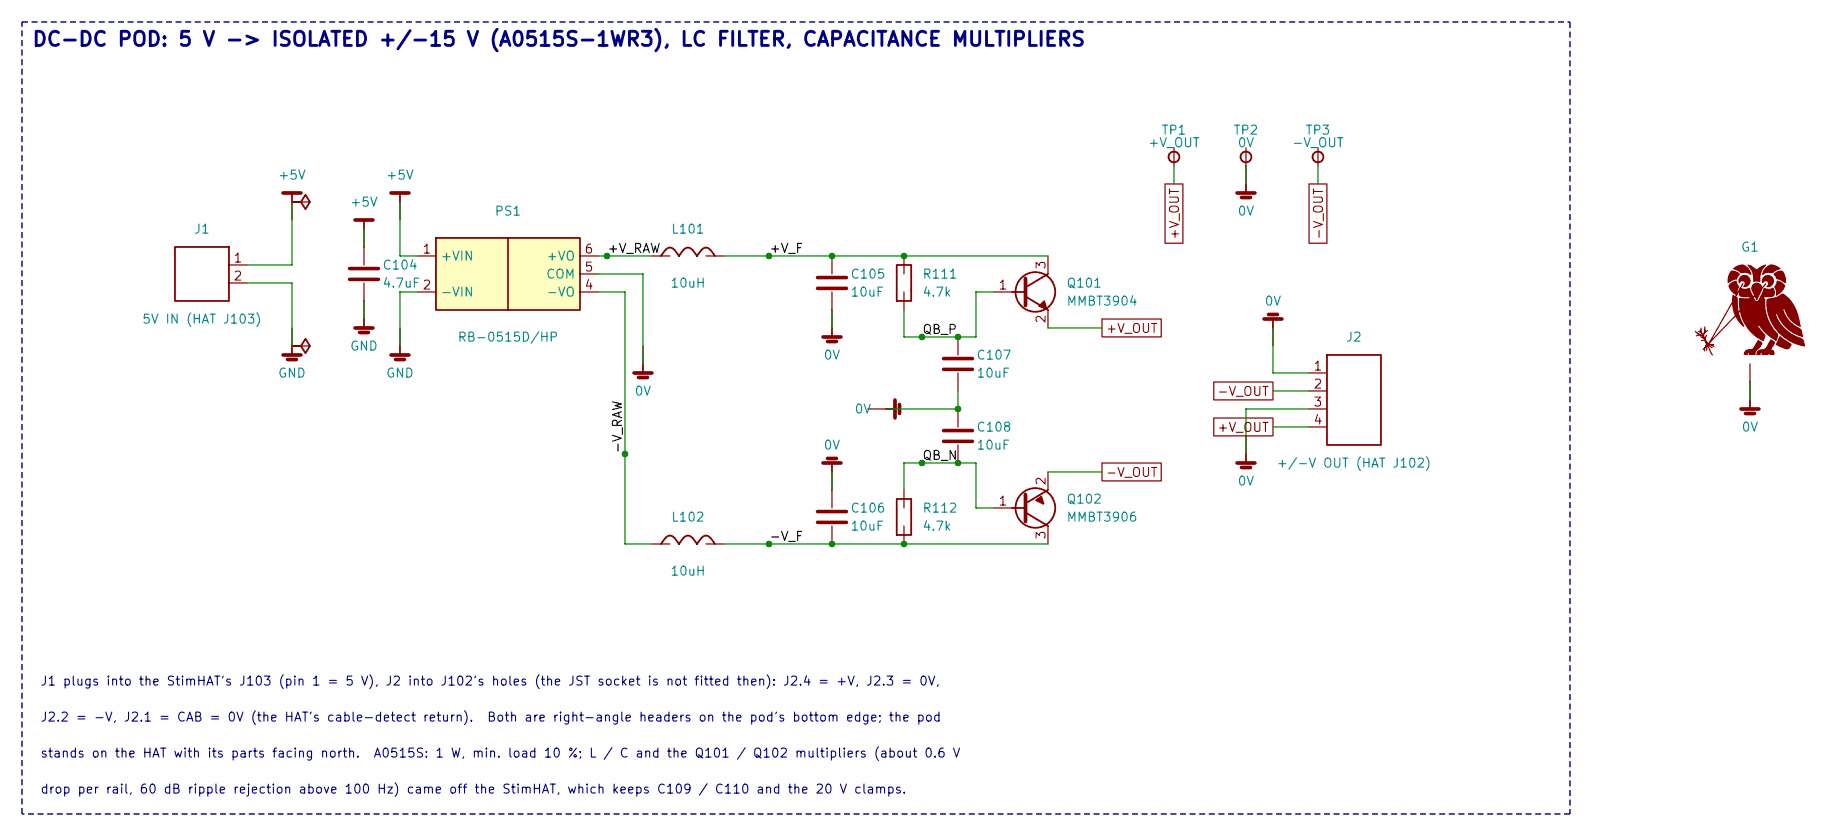
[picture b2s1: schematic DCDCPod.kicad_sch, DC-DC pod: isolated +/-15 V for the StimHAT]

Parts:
C104: 4.7uF; C_0603_1608Metric; LCSC Part # C69335
C105, C106, C107, C108: 10uF; C_0805_2012Metric; LCSC Part # C15850
G1: OwlLogo; OwlLogo_Eyes_6mm_R
J1: 5V IN (HAT J103); PinHeader_1x02_P2.54mm_Horizontal_Pod
J2: +/-V OUT (HAT J102); PinHeader_1x04_P2.00mm_Horizontal_Pod
L101, L102: 10uH; L_0805_2012Metric; LCSC Part # C139245
PS1: RB-0515D/HP; DCDC_SIP6_RB0515D
Q101: MMBT3904; SOT-23; LCSC Part # C20526
Q102: MMBT3906; SOT-23; LCSC Part # C53444
R111, R112: 4.7k; R_0402_1005Metric; LCSC Part # C25900
TP1: +V_OUT; TestPoint_Pad_D1.0mm
TP2: 0V; TestPoint_Pad_D1.0mm
TP3: -V_OUT; TestPoint_Pad_D1.0mm

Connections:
0V: C105.2, C106.1, C107.2, C108.1, G1.1 (GND), J2.1, J2.3, PS1.5 (COM), TP2.1
+5V: C104.1, J1.1, PS1.1 (+VIN)
+V_OUT: J2.4, Q101.2 (E), TP1.1
-V_OUT: J2.2, Q102.2 (E), TP3.1
/+V_F: C105.1, L101.2, Q101.3 (C), R111.1
/+V_RAW: L101.1, PS1.6 (+VO)
/-V_F: C106.2, L102.2, Q102.3 (C), R112.2
/-V_RAW: L102.1, PS1.4 (-VO)
/QB_N: C108.2, Q102.1 (B), R112.1
/QB_P: C107.1, Q101.1 (B), R111.2
GND: C104.2, J1.2, PS1.2 (-VIN)

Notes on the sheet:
DC-DC POD: 5 V -> ISOLATED +/-15 V (A0515S-1WR3), LC FILTER, CAPACITANCE MULTIPLIERS
J1 plugs into the StimHAT's J103 (pin 1 = 5 V), J2 into J102's holes (the JST socket is not fitted then): J2.4 = +V, J2.3 = 0V,
J2.2 = -V, J2.1 = CAB = 0V (the HAT's cable-detect return). Both are right-angle headers on the pod's bottom edge; the pod
stands on the HAT with its parts facing north. A0515S: 1 W, min. load 10 %; L / C and the Q101 / Q102 multipliers (about 0.6 V
drop per rail, 60 dB ripple rejection above 100 Hz) came off the StimHAT, which keeps C109 / C110 and the 20 V clamps.

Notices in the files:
LaserHAT/DCDCPod/DCDCPod.kicad_pcb:
(c)2026 KemereLab
LaserHAT/EStimDaughter/EStimDaughter.kicad_pcb:
(c) 2026.10
hardware/LaserDriverHAT/README.md:
title text and back-side copyright.  A check script (`verify_block.py`, session scratch) confirmed it: 132 / 132 module tracks / vias present
